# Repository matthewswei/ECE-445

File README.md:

# UIUC ECE 445

Senior Design Project Laboratory by UIUC. This repository contains all the documents, files, and code used for Fall 2023 Team 2's project (Ground-Breaking Next-Gen Smart Pet Door). For more information on the project, read the design document inside the repo.

## Team Members

Jeffrey Deng

Norbert Szczotka

Matthew Wei

## TA

Abhisheka Mathur Sekar

## File Information

**Design Document.pdf:** Design document containing all the details about our project

**ECE 445 Proposal.pdf:** Project proposal containing the initial planning and ideas

**Lab Notebook.pdf:** Lab notebook containing weekly updates and progress

**Senior Design RFA:** Initial project approval document

**Team Contract Fulfillment.pdf:** Team contract fulfillment document

**Team Contract.pdf:** Team contract outlying rules

**application.py:** User application code

**camera.c:** Camera module code

**ece445final.kicad_pcb:** PCB layout file for final design

**ece445final.kicad_sch:** Schematic file for final design

**esp32.c:** ESP32 microcontroller code

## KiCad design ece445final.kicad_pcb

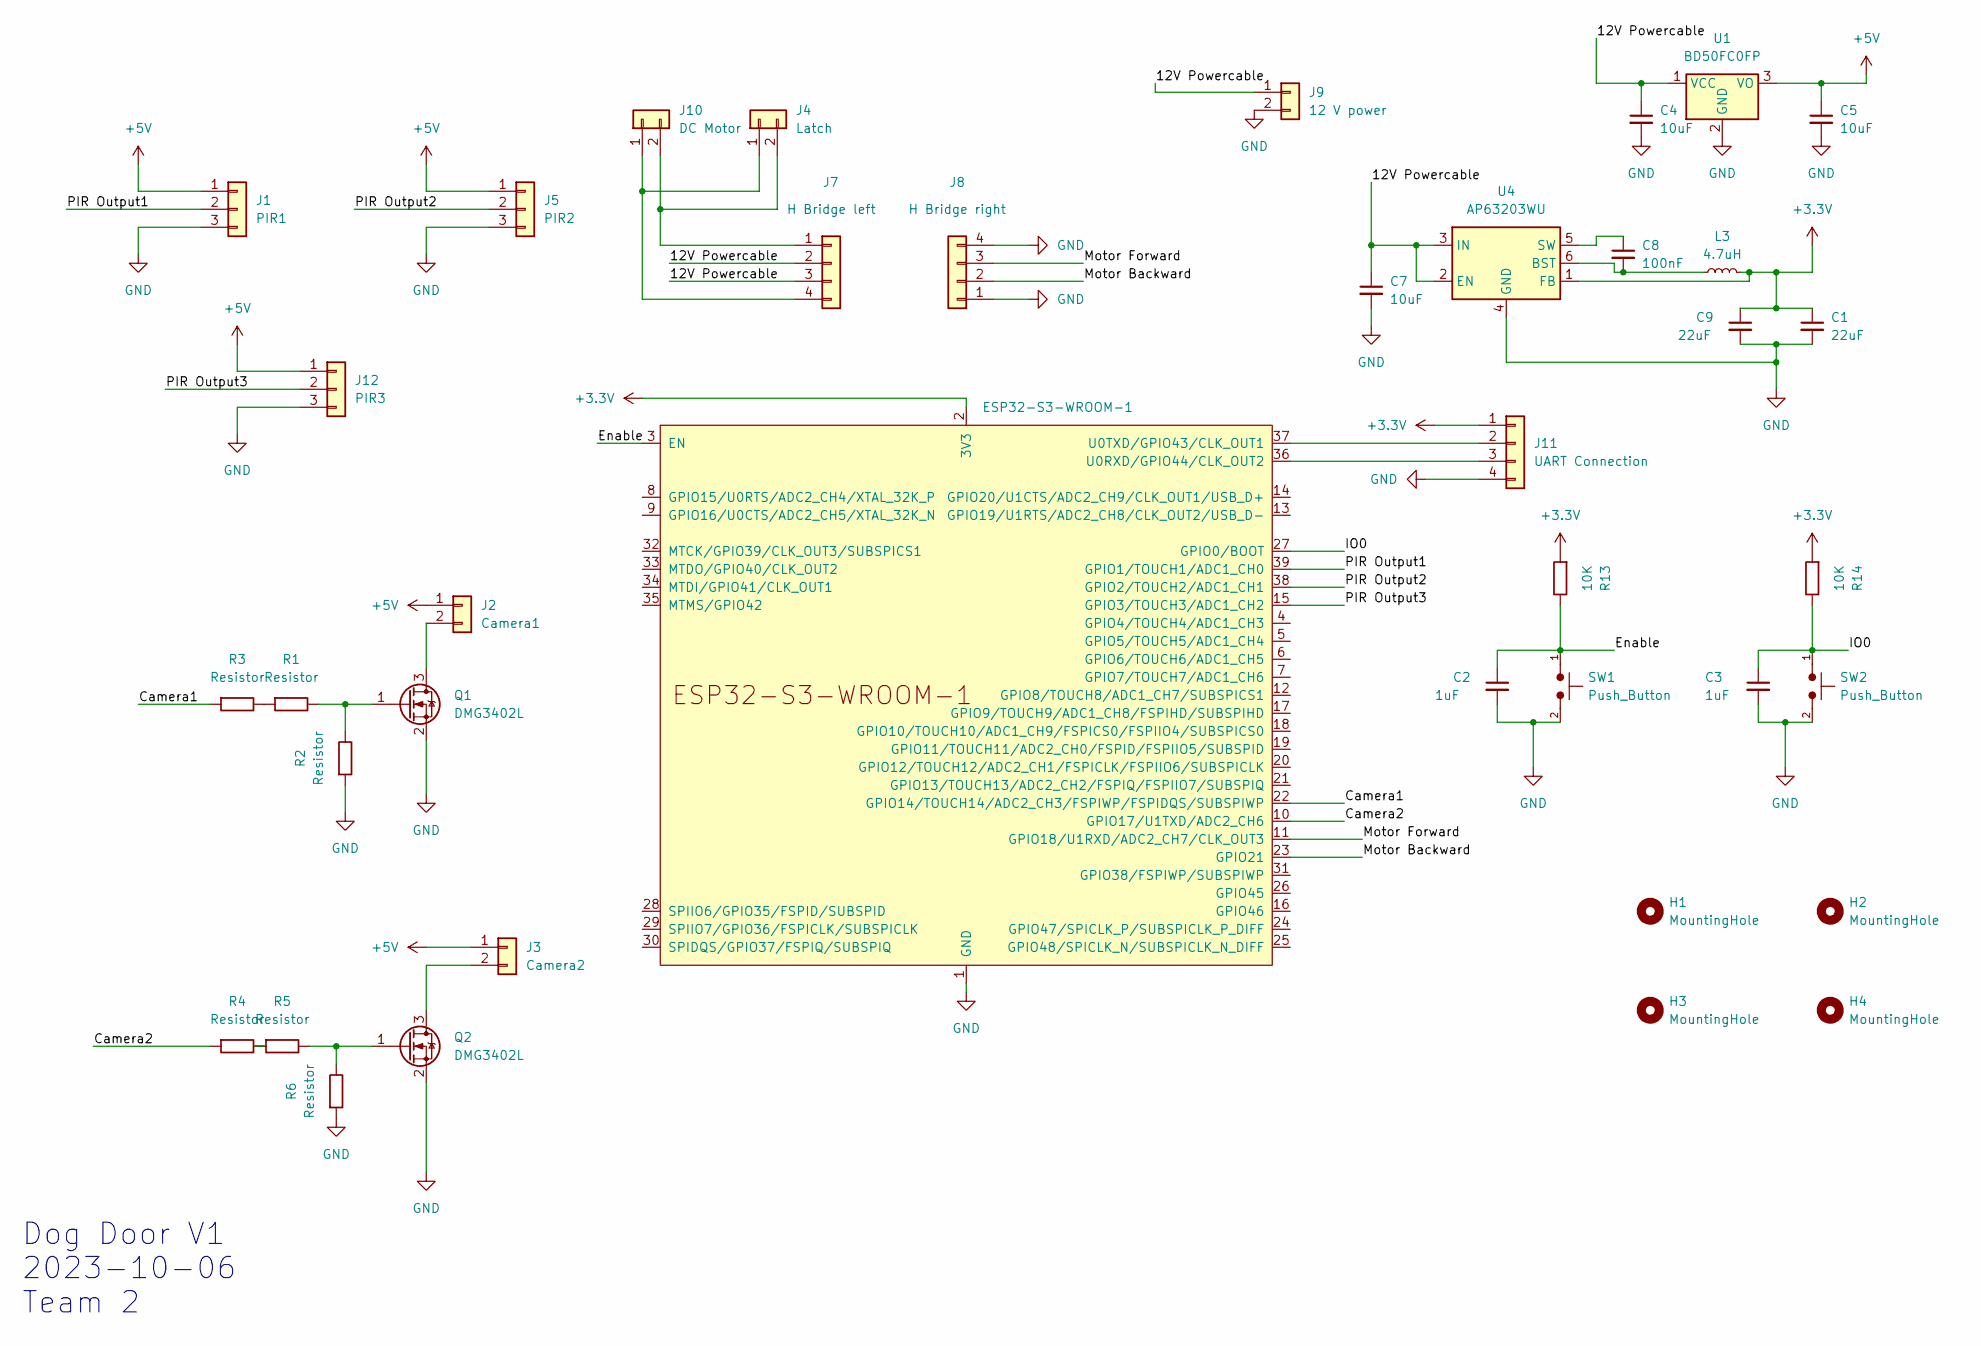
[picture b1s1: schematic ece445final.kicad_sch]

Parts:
C1, C9: 22uF; C_0805_2012Metric_Pad1.18x1.45mm_HandSolder
C2, C3: 1uF; C_0805_2012Metric_Pad1.18x1.45mm_HandSolder
C4, C5, C7: 10uF; C_0805_2012Metric_Pad1.18x1.45mm_HandSolder
C8: 100nF; C_0805_2012Metric_Pad1.18x1.45mm_HandSolder
H1, H2, H3, H4: MountingHole; MountingHole_3.2mm_M3
J1: PIR1; Molex_KK-254_AE-6410-03A_1x03_P2.54mm_Vertical
J2: Camera1; Molex_KK-254_AE-6410-02A_1x02_P2.54mm_Vertical
J3: Camera2; Molex_KK-254_AE-6410-02A_1x02_P2.54mm_Vertical
J4: Latch; Molex_KK-254_AE-6410-02A_1x02_P2.54mm_Vertical
J5: PIR2; Molex_KK-254_AE-6410-03A_1x03_P2.54mm_Vertical
J7: H Bridge left; Molex_KK-254_AE-6410-04A_1x04_P2.54mm_Vertical
J8: H Bridge right; Molex_KK-254_AE-6410-04A_1x04_P2.54mm_Vertical
J9: 12 V power; Molex_KK-254_AE-6410-02A_1x02_P2.54mm_Vertical
J10: DC Motor; Molex_KK-254_AE-6410-02A_1x02_P2.54mm_Vertical
J11: UART Connection; Molex_KK-254_AE-6410-04A_1x04_P2.54mm_Vertical
J12: PIR3; Molex_KK-254_AE-6410-03A_1x03_P2.54mm_Vertical
L3: 4.7uH; L_0805_2012Metric_Pad1.15x1.40mm_HandSolder
Q1, Q2: DMG3402L; SOT-23
R1, R2, R3, R4, R5, R6: Resistor; R_0805_2012Metric_Pad1.20x1.40mm_HandSolder
R13, R14: 10K; R_0805_2012Metric_Pad1.20x1.40mm_HandSolder
SW1, SW2: Push_Button; SW_PUSH_6mm
U1: BD50FC0FP; TO-252-2
U2: ESP32-S3-WROOM-1
U4: AP63203WU; TSOT-23-6

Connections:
+3.3V: C1.1, C9.1, J11.1, L3.2, R13.1, R14.1, U2.2 (3V3), U4.1 (FB)
+5V: C5.1, J1.1, J2.1, J3.1, J5.1, J12.1, U1.3 (VO)
/12V Powercable: C4.1, C7.1, J7.2, J7.3, J9.1, U1.1 (VCC), U4.2 (EN), U4.3 (IN)
/Camera1: R3.1, U2.22 (GPIO14/TOUCH14/ADC2_CH3/FSPIWP/FSPIDQS/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)
/Camera2: R4.1, U2.10 (GPIO17/U1TXD/ADC2_CH6)
/Enable: C2.1, R13.2, SW1.1, U2.3 (EN)
/IO0: C3.1, R14.2, SW2.1, U2.27 (GPIO0/BOOT)
/Motor Backward: J8.2, U2.23 (GPIO21)
/Motor Forward: J8.3, U2.11 (GPIO18/U1RXD/ADC2_CH7/CLK_OUT3)
/PIR Output1: J1.2, U2.39 (GPIO1/TOUCH1/ADC1_CH0)
/PIR Output2: J5.2, U2.38 (GPIO2/TOUCH2/ADC1_CH1)
/PIR Output3: J12.2, U2.15 (GPIO3/TOUCH3/ADC1_CH2)
GND: C1.2, C2.2, C3.2, C4.2, C5.2, C7.2, C9.2, J1.3, J5.3, J8.1, J8.4, J9.2, J11.4, J12.3, Q1.2 (S), Q2.2 (S), R2.1, R6.1, SW1.2, SW2.2, U1.2 (GND), U2.1 (GND), U2.40 (GND), U2.41 (GND), U4.4 (GND)
unnamed: J2.2, Q1.3 (D)
unnamed: J3.2, Q2.3 (D)
unnamed: J4.1, J7.4, J10.1
unnamed: J4.2, J7.1, J10.2
unnamed: J11.2, U2.37 (U0TXD/GPIO43/CLK_OUT1)
unnamed: J11.3, U2.36 (U0RXD/GPIO44/CLK_OUT2)
unnamed: Q1.1 (G), R1.2, R2.2
unnamed: Q2.1 (G), R5.2, R6.2
unnamed: R1.1, R3.2
unnamed: R4.2, R5.1
unnamed: C8.2, L3.1, U4.6 (BST)
unnamed: C8.1, U4.5 (SW)

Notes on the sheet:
Dog Door V1 2023-10-06 Team 2

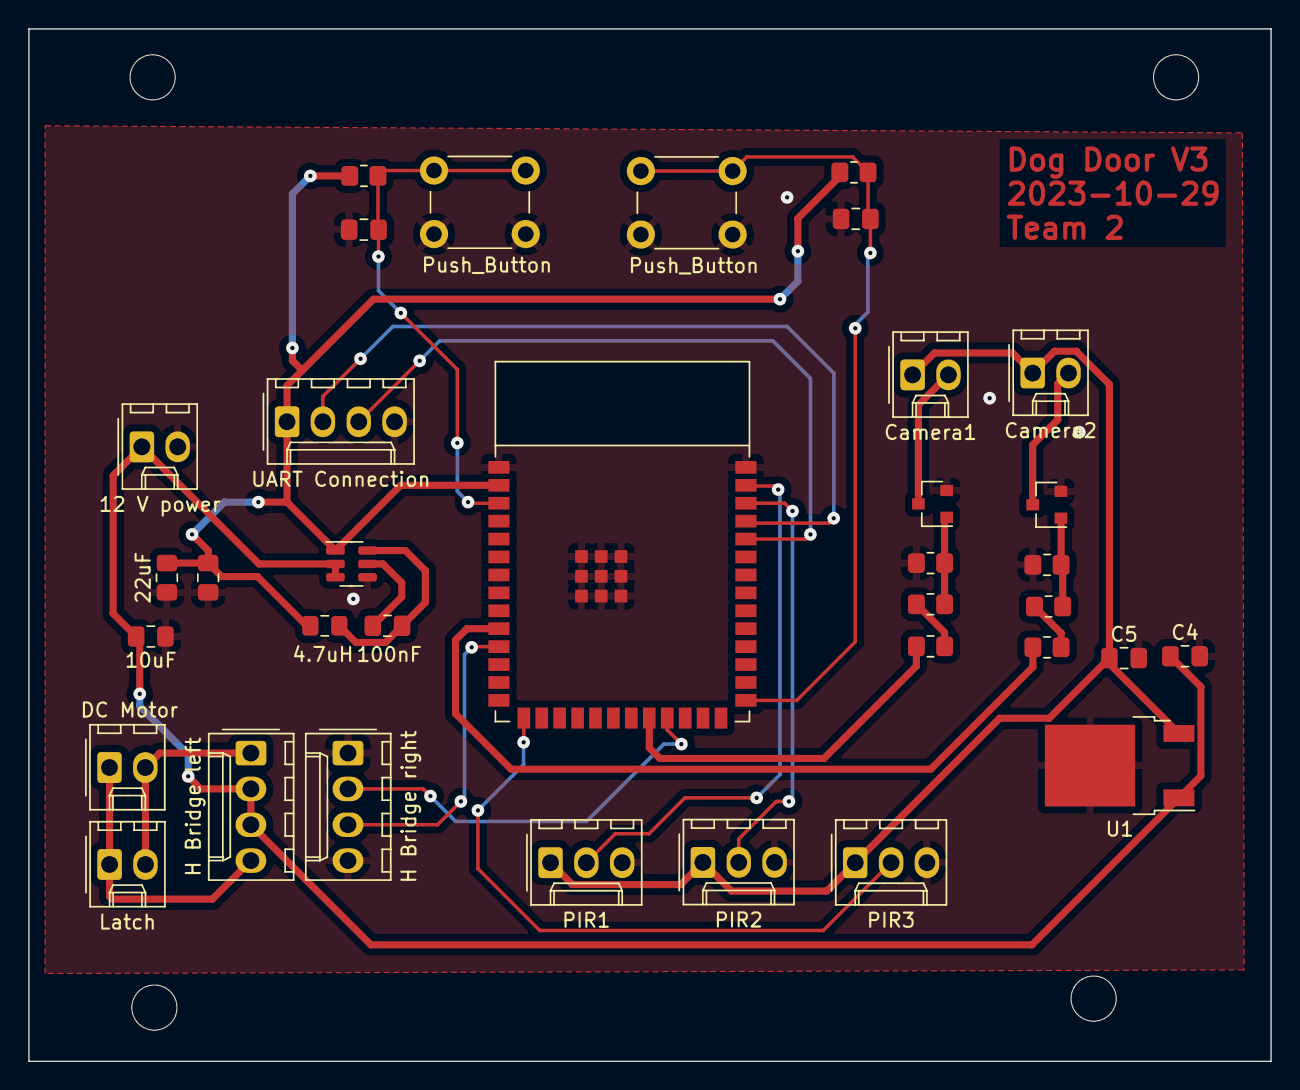
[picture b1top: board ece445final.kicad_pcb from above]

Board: 2 copper layers, 88.0 x 73.2 mm, 39 parts (0 on the bottom side), 25 nets.

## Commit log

2023-11-28 initial file upload
2023-11-28 code upload
